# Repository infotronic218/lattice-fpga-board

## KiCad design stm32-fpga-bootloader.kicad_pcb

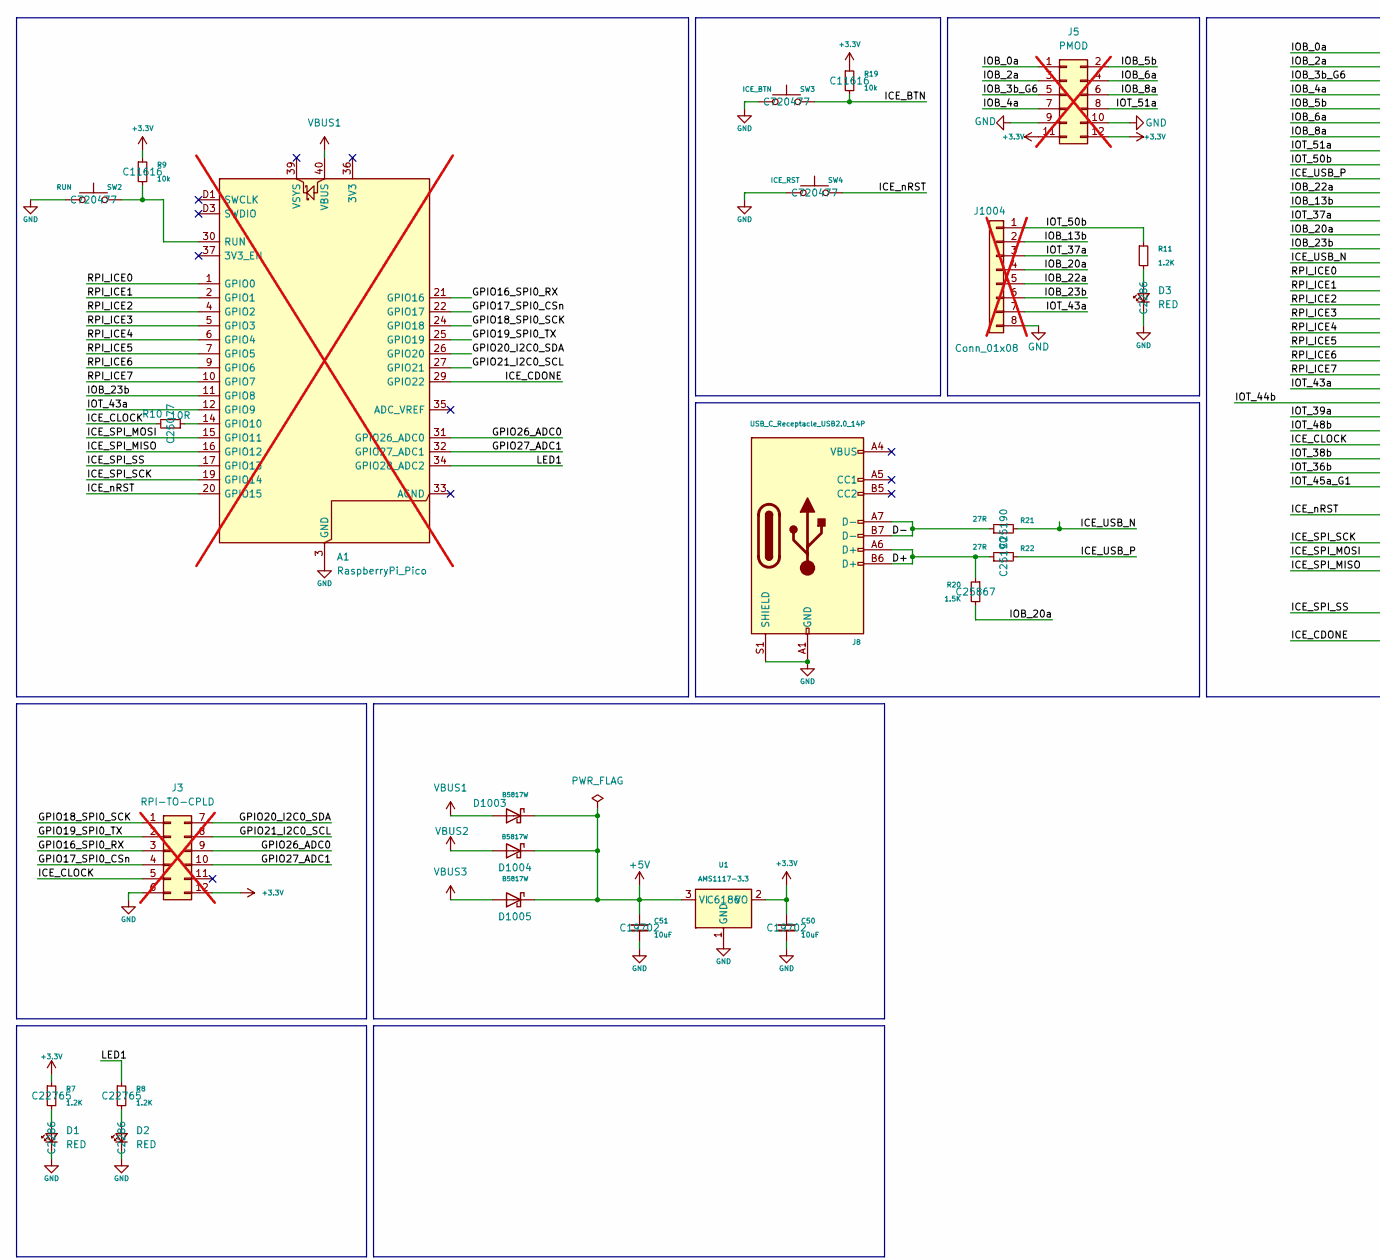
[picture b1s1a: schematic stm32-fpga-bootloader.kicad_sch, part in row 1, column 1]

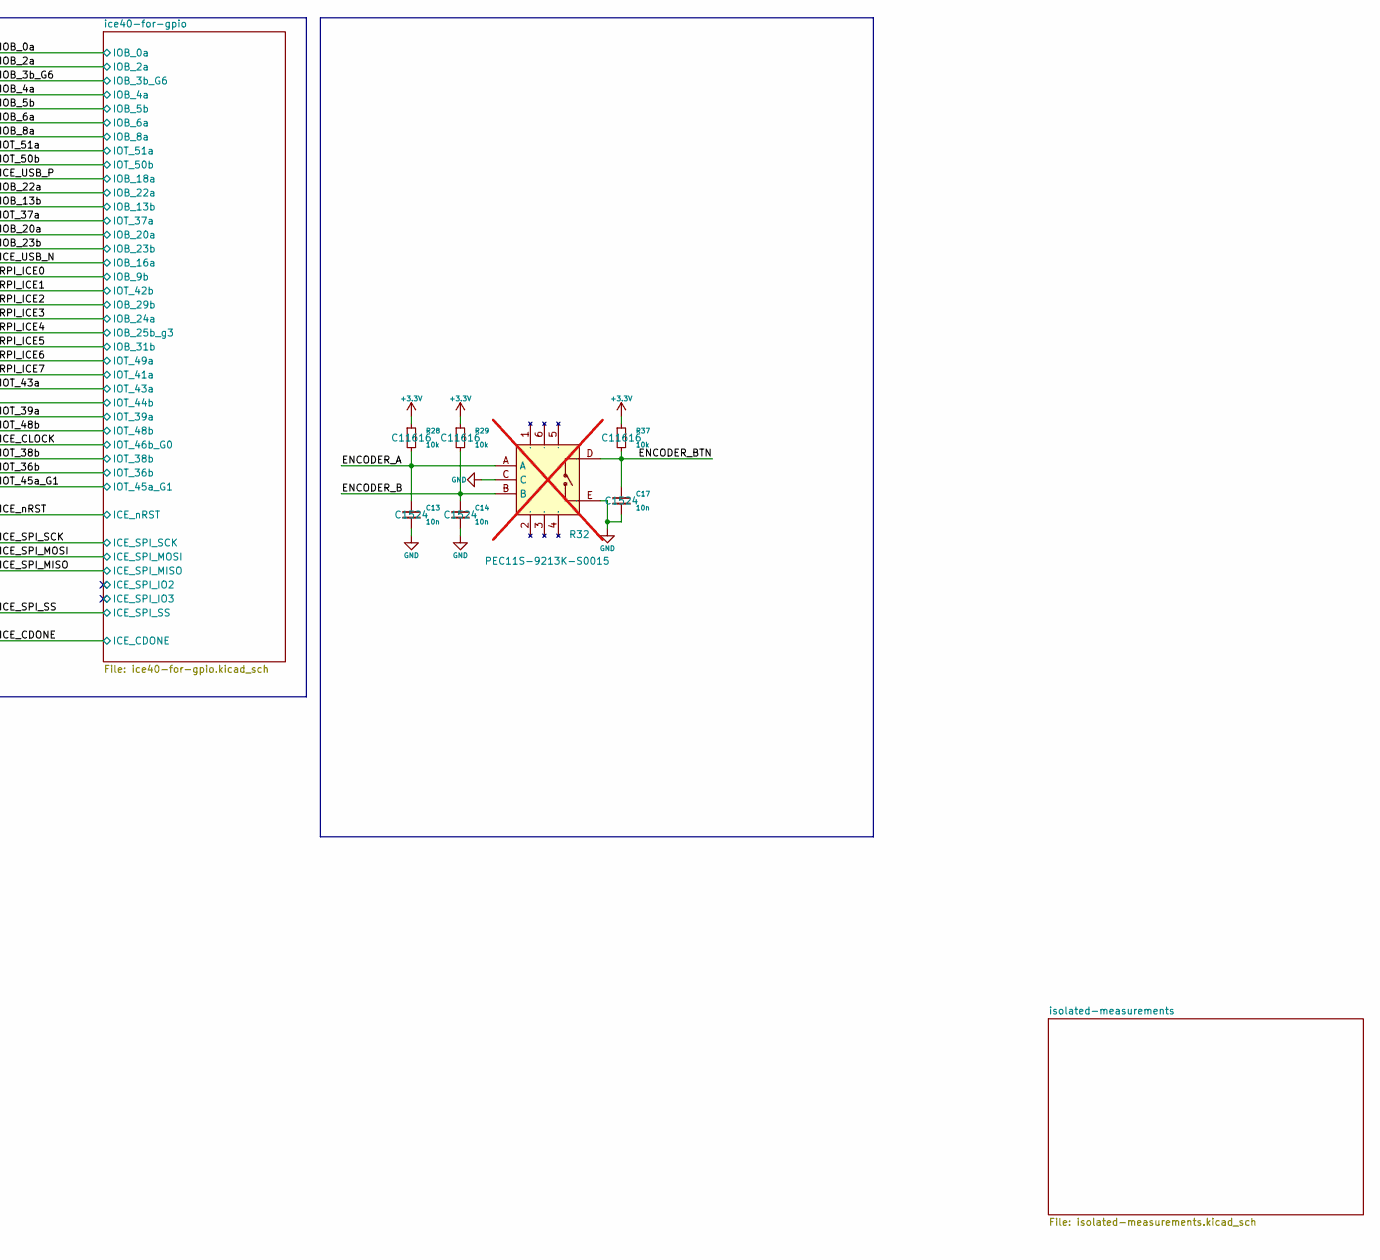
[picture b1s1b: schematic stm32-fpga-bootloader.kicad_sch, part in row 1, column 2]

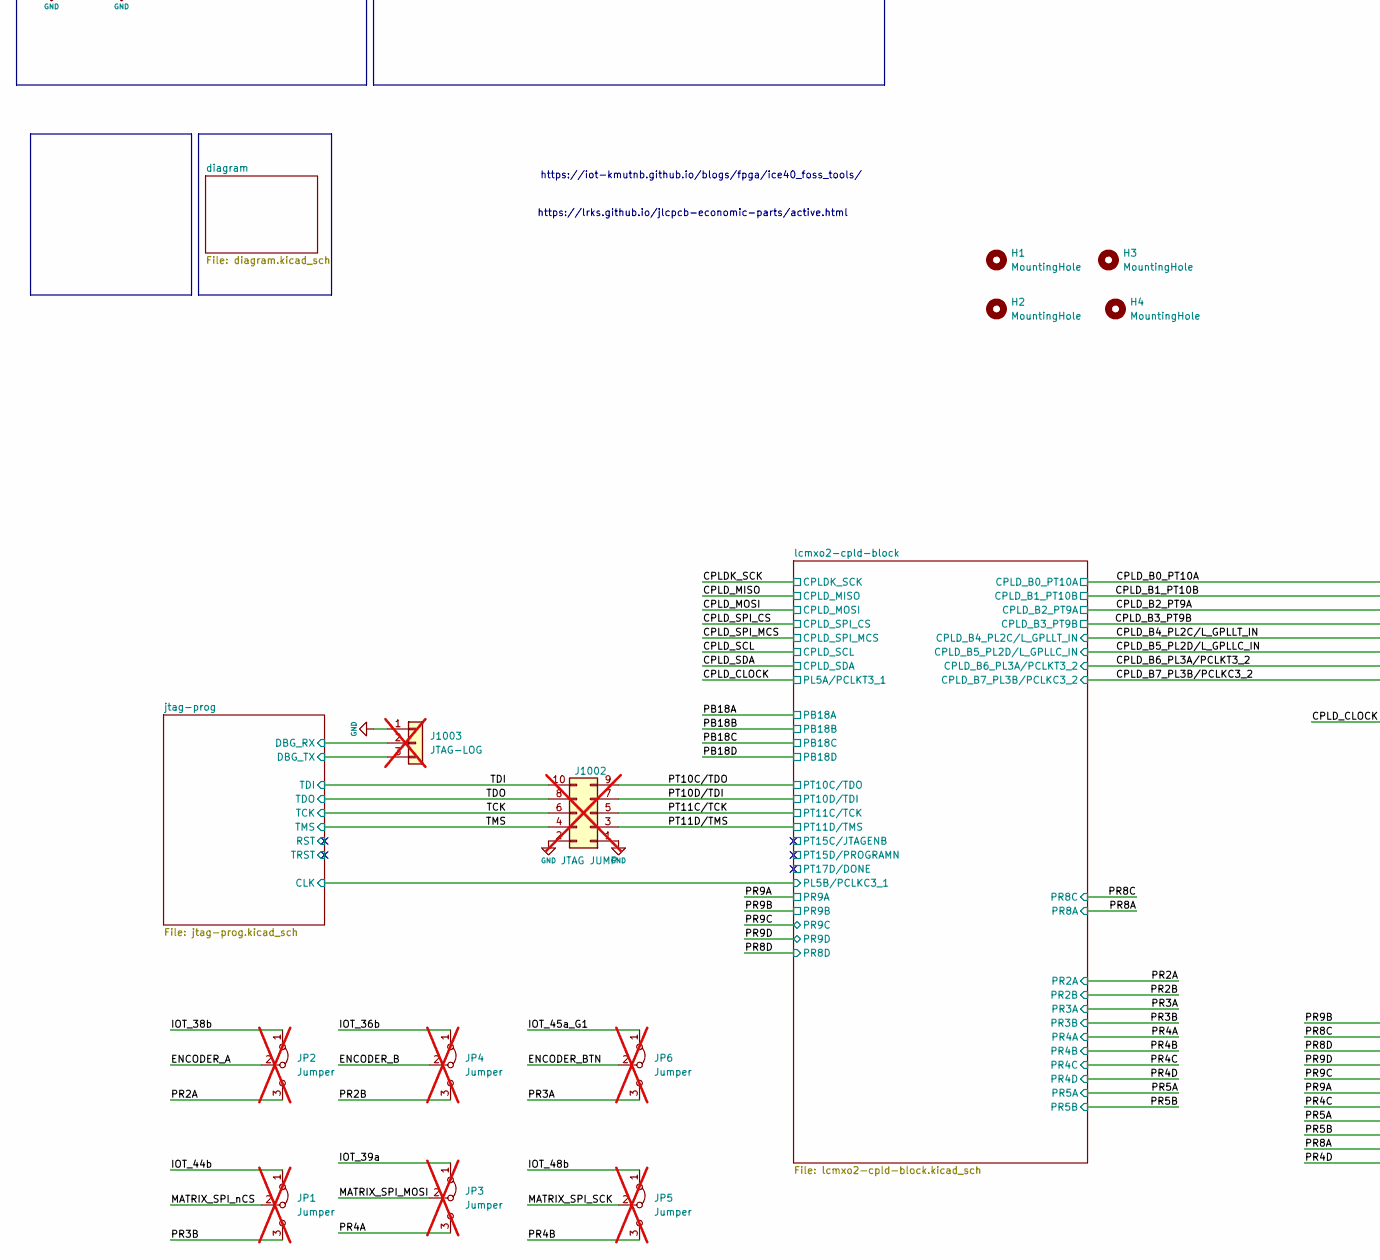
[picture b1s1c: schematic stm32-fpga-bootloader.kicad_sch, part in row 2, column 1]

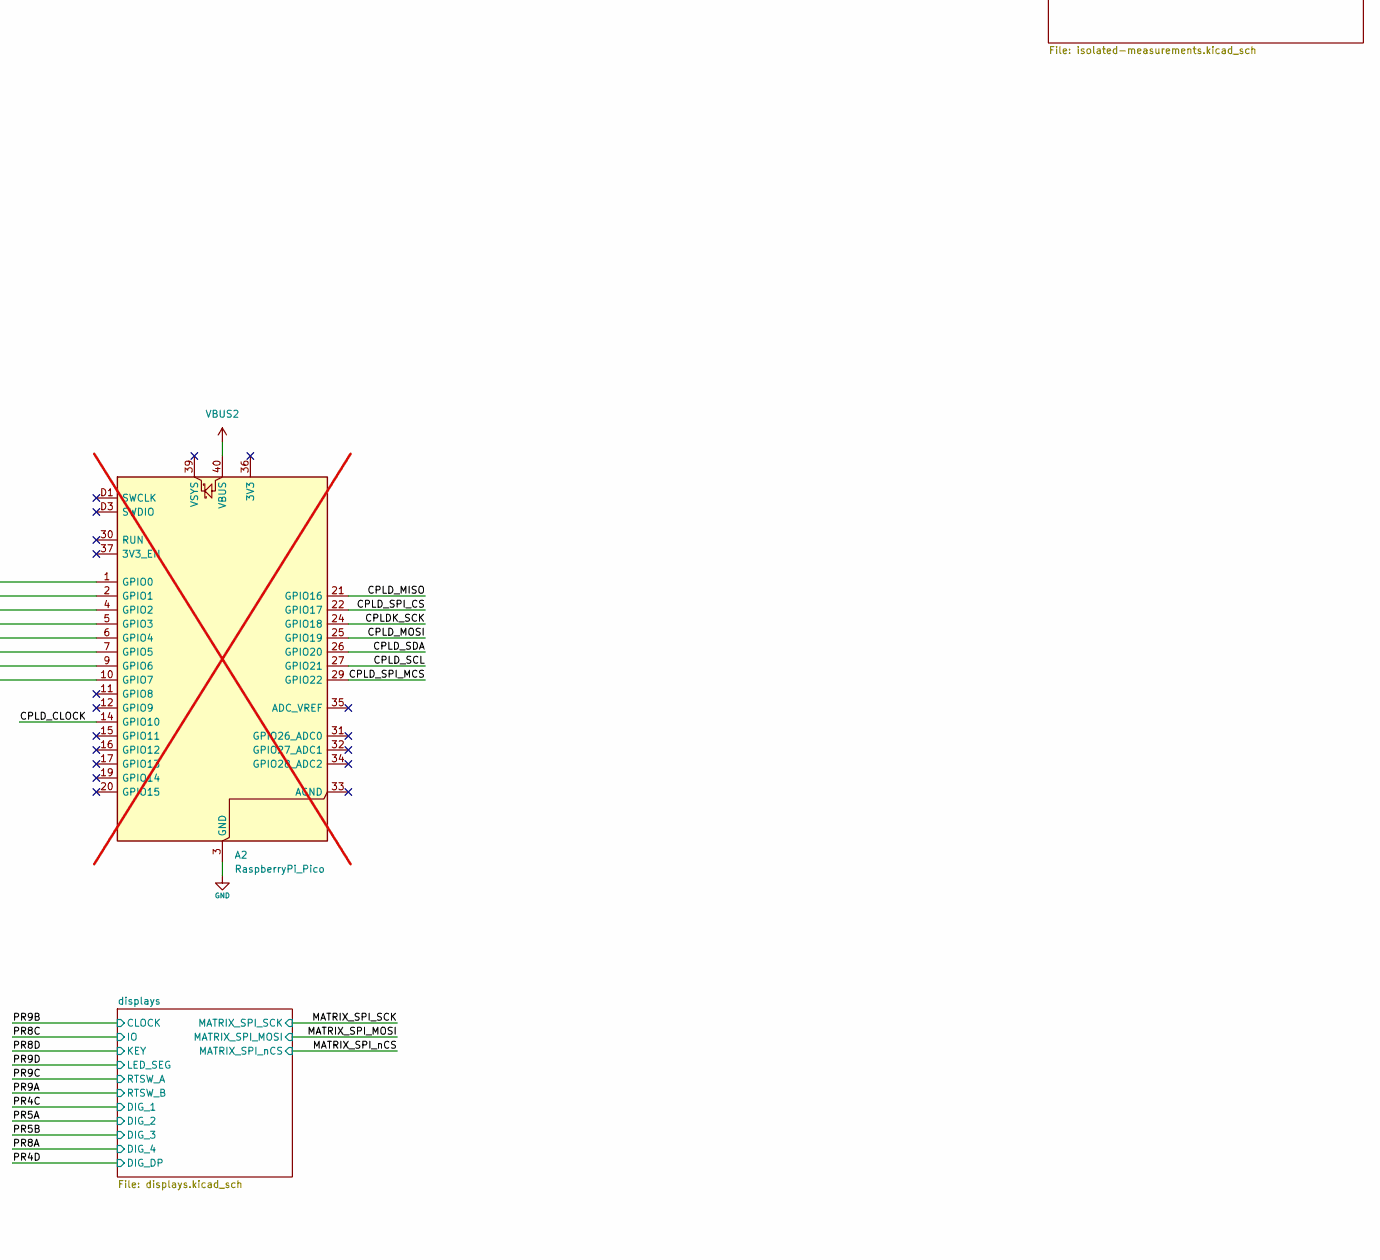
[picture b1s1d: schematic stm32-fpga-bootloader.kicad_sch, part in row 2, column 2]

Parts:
A1, A2: RaspberryPi_Pico; RaspberryPi_Pico_Common_THT; not fitted
C13, C14, C17: 10n; C_0402_1005Metric; LCSC C1524
C50, C51: 10uF; C_0603_1608Metric; LCSC C19702
D1, D2, D3: RED; LED_0603_1608Metric; LCSC C2286
D1003, D1004, D1005: B5817W; D_SOD-123; LCSC C7420328
H1, H2, H3, H4: MountingHole; MountingHole_3.2mm_M3
J3: RPI-TO-CPLD; PinHeader_2x06_P2.54mm_Vertical; not fitted
J5: PMOD; PinSocket_2x06_P2.54mm_Horizontal; not fitted
J8: USB_C_Receptacle_USB2.0_14P; USB_C_Receptacle_G-Switch_GT-USB-7010ASV
J1002: JTAG JUMP; PinSocket_2x05_P2.54mm_Vertical; not fitted
J1003: JTAG-LOG; PinSocket_1x03_P2.54mm_Vertical; not fitted
J1004: Conn_01x08; PinHeader_1x08_P2.54mm_Vertical; not fitted
JP1, JP2, JP3, JP4, JP5, JP6: Jumper; PinSocket_1x03_P1.27mm_Vertical; not fitted
R7, R8, R11: 1.2K; R_0603_1608Metric; LCSC C22765
R9, R19, R28, R29, R37: 10k; R_0402_1005Metric; LCSC C11616
R10: 10R; R_0402_1005Metric; LCSC C25077
R20: 1.5K; R_0402_1005Metric; LCSC C25867
R21, R22: 27R; R_0603_1608Metric; LCSC C25190
R32: PEC11S-9213K-S0015; RES-ADJ-SMD_PEC11S-9213K-S0015; LCSC Part Name PEC11S-9213K-S0015; not fitted
SW2: RUN; SW-SMD_L3.9-W3.0-P4.45; LCSC C720477
SW3: ICE_BTN; SW-SMD_L3.9-W3.0-P4.45; LCSC C720477
SW4: ICE_RST; SW-SMD_L3.9-W3.0-P4.45; LCSC C720477
U1: AMS1117-3.3; SOT-223-3_TabPin2; LCSC C6186

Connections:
+3.3V: C50.1, J3.12, J5.11, J5.12, R7.1, R9.1, R19.1, R28.1, R29.1, R37.1, U1.2 (VO); also elsewhere on the board
+5V: C51.1, D1003.1, D1004.1, D1005.1, U1.3 (VI); also elsewhere on the board
/CPLDK_SCK: A2.24 (GPIO18); also elsewhere on the board
/CPLD_B0_PT10A: A2.1 (GPIO0); also elsewhere on the board
/CPLD_B1_PT10B: A2.2 (GPIO1); also elsewhere on the board
/CPLD_B2_PT9A: A2.4 (GPIO2); also elsewhere on the board
/CPLD_B3_PT9B: A2.5 (GPIO3); also elsewhere on the board
/CPLD_B4_PL2C/L_GPLLT_IN: A2.6 (GPIO4); also elsewhere on the board
/CPLD_B5_PL2D/L_GPLLC_IN: A2.7 (GPIO5); also elsewhere on the board
/CPLD_B6_PL3A/PCLKT3_2: A2.9 (GPIO6); also elsewhere on the board
/CPLD_B7_PL3B/PCLKC3_2: A2.10 (GPIO7); also elsewhere on the board
/CPLD_CLOCK: A2.14 (GPIO10); also elsewhere on the board
/CPLD_MISO: A2.21 (GPIO16); also elsewhere on the board
/CPLD_MOSI: A2.25 (GPIO19); also elsewhere on the board
/CPLD_SCL: A2.27 (GPIO21); also elsewhere on the board
/CPLD_SDA: A2.26 (GPIO20); also elsewhere on the board
/CPLD_SPI_CS: A2.22 (GPIO17); also elsewhere on the board
/CPLD_SPI_MCS: A2.29 (GPIO22); also elsewhere on the board
/D+: J8.A6 (D+), J8.B6 (D+), R20.1, R22.1
/D-: J8.A7 (D-), J8.B7 (D-), R21.1
/ENCODER_A: C13.1, JP2.2 (C), R28.2, R32.A
/ENCODER_B: C14.1, JP4.2 (C), R29.2, R32.B
/ENCODER_BTN: C17.1, JP6.2 (C), R32.D, R37.2
/GPIO16_SPI0_RX: A1.21 (GPIO16), J3.3
/GPIO17_SPI0_CSn: A1.22 (GPIO17), J3.4
/GPIO18_SPI0_SCK: A1.24 (GPIO18), J3.1
/GPIO19_SPI0_TX: A1.25 (GPIO19), J3.2
/GPIO20_I2C0_SDA: A1.26 (GPIO20), J3.7
/GPIO21_I2C0_SCL: A1.27 (GPIO21), J3.8
/GPIO26_ADC0: A1.31 (GPIO26_ADC0), J3.9
/GPIO27_ADC1: A1.32 (GPIO27_ADC1), J3.10
/ICE_BTN: R19.2, SW3.2
/ICE_CDONE: A1.29 (GPIO22); also elsewhere on the board
/ICE_CLOCK: J3.5, R10.2; also elsewhere on the board
/ICE_SPI_MISO: A1.16 (GPIO12); also elsewhere on the board
/ICE_SPI_MOSI: A1.15 (GPIO11); also elsewhere on the board
/ICE_SPI_SCK: A1.19 (GPIO14); also elsewhere on the board
/ICE_SPI_SS: A1.17 (GPIO13); also elsewhere on the board
/ICE_USB_N: R21.2; also elsewhere on the board
/ICE_USB_P: R22.2; also elsewhere on the board
/ICE_nRST: A1.20 (GPIO15), SW4.2; also elsewhere on the board
/IOB_0a: J5.1; also elsewhere on the board
/IOB_2a: J5.3; also elsewhere on the board
/IOB_3b_G6: J5.5; also elsewhere on the board
/IOB_4a: J5.7; also elsewhere on the board
/IOB_5b: J5.2; also elsewhere on the board
/IOB_6a: J5.4; also elsewhere on the board
/IOB_8a: J5.6; also elsewhere on the board
/IOB_13b: J1004.2; also elsewhere on the board
/IOB_20a: J1004.4, R20.2; also elsewhere on the board
/IOB_22a: J1004.5; also elsewhere on the board
/IOB_23b: A1.11 (GPIO8), J1004.6; also elsewhere on the board
/IOT_36b: JP4.1 (A); also elsewhere on the board
/IOT_37a: J1004.3; also elsewhere on the board
/IOT_38b: JP2.1 (A); also elsewhere on the board
/IOT_39a: JP3.1 (A); also elsewhere on the board
/IOT_43a: A1.12 (GPIO9), J1004.7; also elsewhere on the board
/IOT_44b: JP1.1 (A); also elsewhere on the board
/IOT_45a_G1: JP6.1 (A); also elsewhere on the board
/IOT_48b: JP5.1 (A); also elsewhere on the board
/IOT_50b: J1004.1, R11.1; also elsewhere on the board
/IOT_51a: J5.8; also elsewhere on the board
/LED1: A1.34 (GPIO28_ADC2), R8.1
/MATRIX_SPI_MOSI: JP3.2 (C); also elsewhere on the board
/MATRIX_SPI_SCK: JP5.2 (C); also elsewhere on the board
/MATRIX_SPI_nCS: JP1.2 (C); also elsewhere on the board
/PR2A: JP2.3 (B); also elsewhere on the board
/PR2B: JP4.3 (B); also elsewhere on the board
/PR3A: JP6.3 (B); also elsewhere on the board
/PR3B: JP1.3 (B); also elsewhere on the board
/PR4A: JP3.3 (B); also elsewhere on the board
/PR4B: JP5.3 (B); also elsewhere on the board
/PT10C/TDO: J1002.9; also elsewhere on the board
/PT10D/TDI: J1002.7; also elsewhere on the board
/PT11C/TCK: J1002.5; also elsewhere on the board
/PT11D/TMS: J1002.3; also elsewhere on the board
/RPI_ICE0: A1.1 (GPIO0); also elsewhere on the board
/RPI_ICE1: A1.2 (GPIO1); also elsewhere on the board
/RPI_ICE2: A1.4 (GPIO2); also elsewhere on the board
/RPI_ICE3: A1.5 (GPIO3); also elsewhere on the board
/RPI_ICE4: A1.6 (GPIO4); also elsewhere on the board
/RPI_ICE5: A1.7 (GPIO5); also elsewhere on the board
/RPI_ICE6: A1.9 (GPIO6); also elsewhere on the board
/RPI_ICE7: A1.10 (GPIO7); also elsewhere on the board
/TCK: J1002.6; also elsewhere on the board
/TDI: J1002.10; also elsewhere on the board
/TDO: J1002.8; also elsewhere on the board
/TMS: J1002.4; also elsewhere on the board
/jtag-prog/DBG_RX: J1003.2; also elsewhere on the board
/jtag-prog/DBG_TX: J1003.3; also elsewhere on the board
GND: A1.3 (GND), A1.8 (GND), A1.13 (GND), A1.18 (GND), A1.23 (GND), A1.28 (GND), A1.38 (GND), A1.D2 (GND), A2.3 (GND), A2.8 (GND), A2.13 (GND), A2.18 (GND), A2.23 (GND), A2.28 (GND), A2.38 (GND), A2.D2 (GND), C13.2, C14.2, C17.2, C50.2, C51.2, D1.1 (K), D2.1 (K), D3.1 (K), J3.6, J5.9, J5.10, J8.A1 (GND), J8.A12 (GND), J8.B1 (GND), J8.B12 (GND), J8.S1 (SHIELD), J1002.1, J1002.2, J1003.1, J1004.8, R32.C, R32.E, SW2.1, SW3.1, SW4.1, U1.1 (GND); also elsewhere on the board
unnamed: A1.14 (GPIO10), R10.1
unnamed: A1.30 (RUN), R9.2, SW2.2
unnamed: D1.2 (A), R7.2
unnamed: D2.2 (A), R8.2
unnamed: D3.2 (A), R11.2
VBUS1: A1.40 (VBUS), D1003.2
VBUS2: A2.40 (VBUS), D1004.2
VBUS3: D1005.2; also elsewhere on the board

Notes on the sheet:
https://iot-kmutnb.github.io/blogs/fpga/ice40_foss_tools/
https://lrks.github.io/jlcpcb-economic-parts/active.html

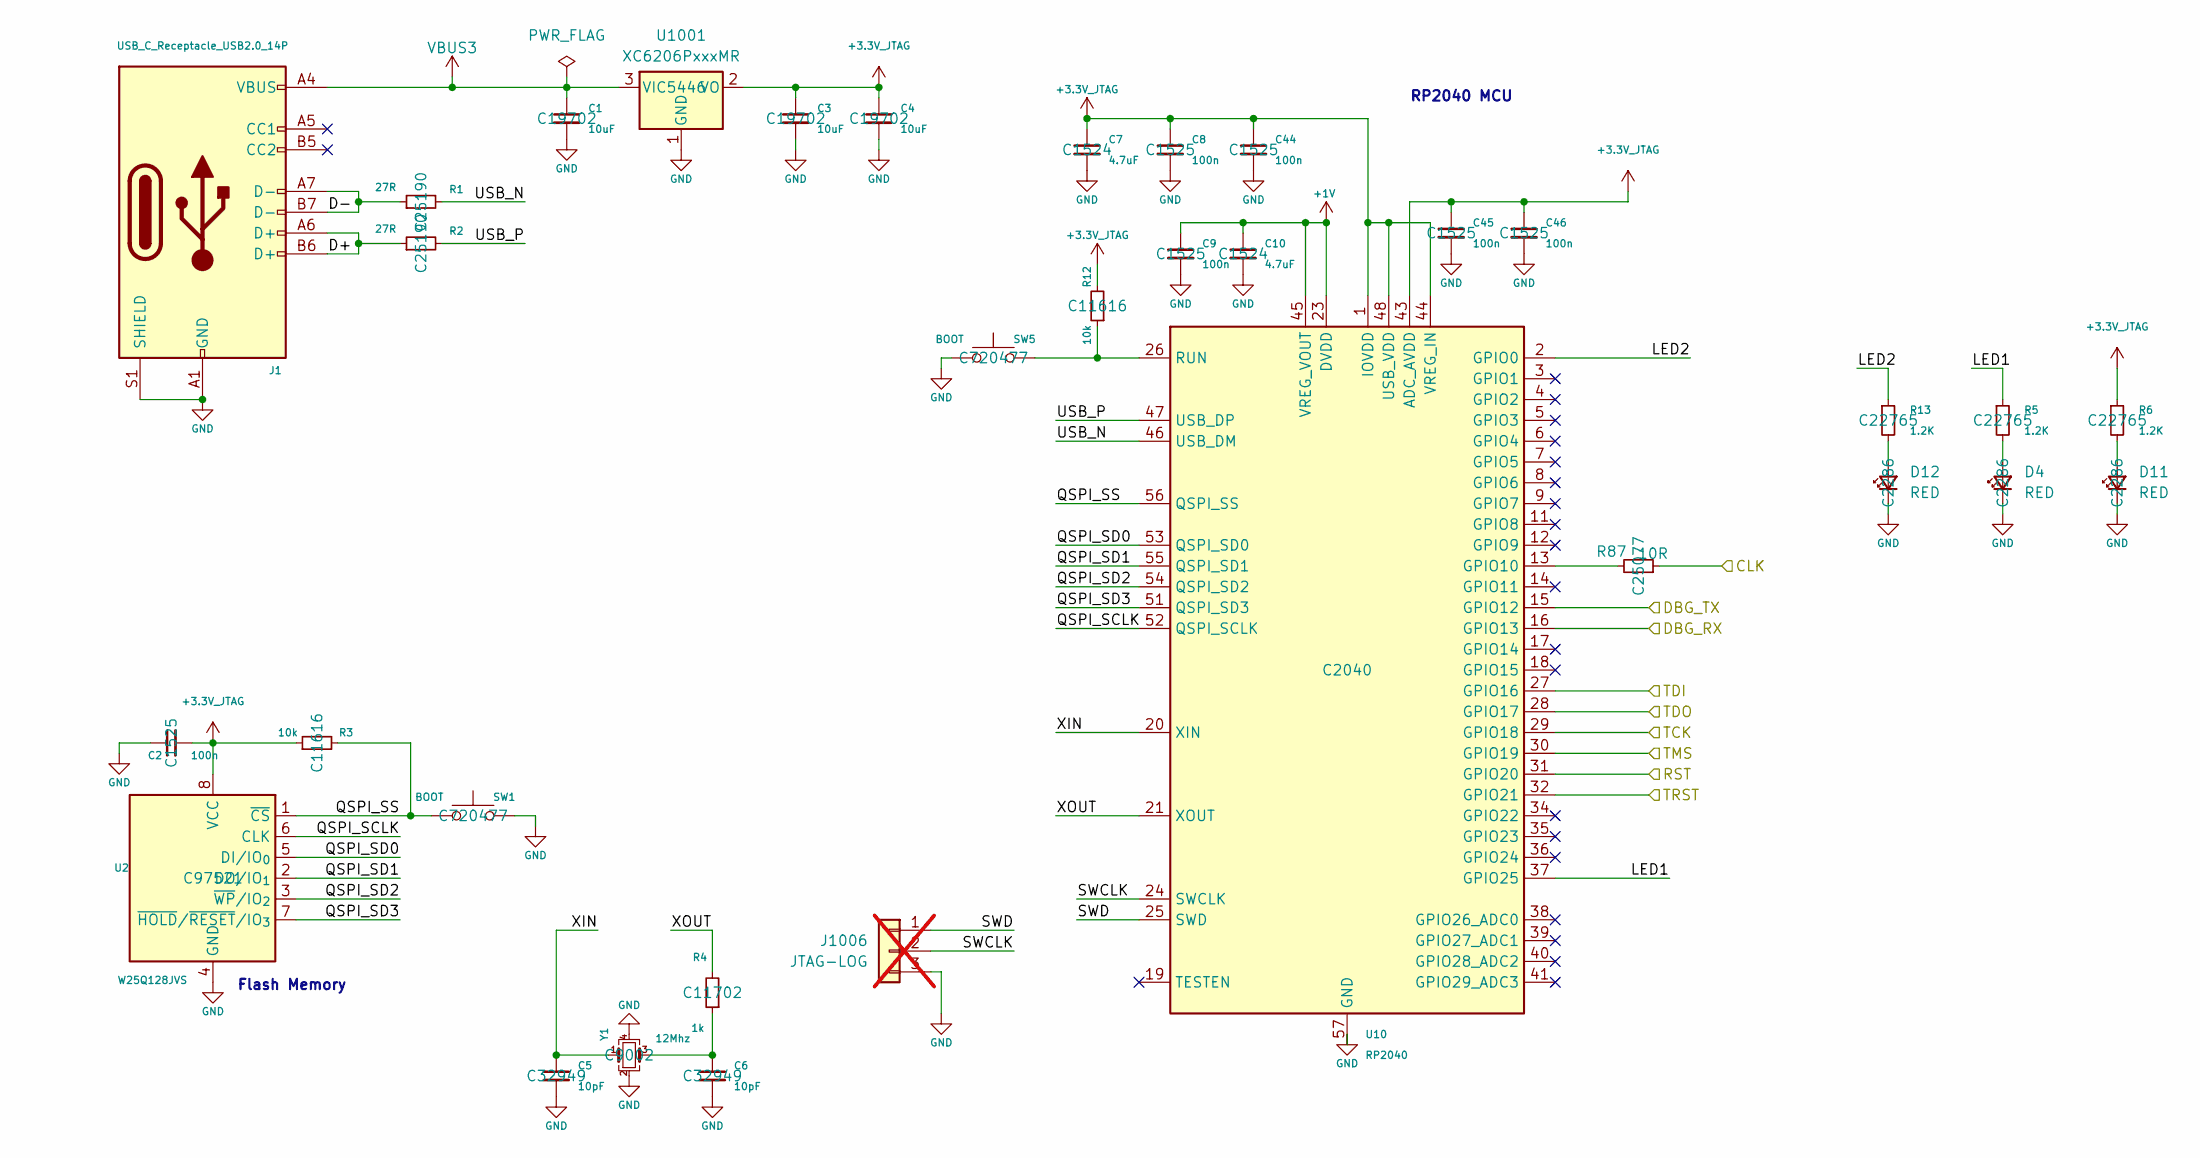
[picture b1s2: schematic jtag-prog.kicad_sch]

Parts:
C1, C3, C4: 10uF; C_0603_1608Metric; LCSC C19702
C2, C8, C9, C44, C45, C46: 100n; C_0402_1005Metric; LCSC C1525
C5, C6: 10pF; C_0402_1005Metric; LCSC C32949
C7, C10: 4.7uF; C_0603_1608Metric; LCSC C1524
D4, D11, D12: RED; LED_0603_1608Metric; LCSC C2286
J1: USB_C_Receptacle_USB2.0_14P; USB_C_Receptacle_G-Switch_GT-USB-7010ASV
J1006: JTAG-LOG; PinSocket_1x03_P2.54mm_Vertical; not fitted
R1, R2: 27R; R_0603_1608Metric; LCSC C25190
R3, R12: 10k; R_0402_1005Metric; LCSC C11616
R4: 1k; R_0402_1005Metric; LCSC C11702
R5, R6, R13: 1.2K; R_0603_1608Metric; LCSC C22765
R87: 10R; R_0402_1005Metric; LCSC C25077
SW1, SW5: BOOT; SW-SMD_L3.9-W3.0-P4.45; LCSC C720477
U2: W25Q128JVS; SOIC-8_5.3x5.3mm_P1.27mm; LCSC C97521
U10: RP2040; QFN-56-1EP_7x7mm_P0.4mm_EP3.2x3.2mm; LCSC C2040
U1001: XC6206PxxxMR; SOT-23-3; LCSC C5446
Y1: 12Mhz; Crystal_SMD_3225-4Pin_3.2x2.5mm; LCSC C9002

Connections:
+1V: C9.1, C10.1, U10.23 (DVDD), U10.45 (VREG_VOUT), U10.50 (DVDD)
+3.3V_JTAG: C2.2, C3.1, C4.1, C7.1, C8.1, C44.1, C45.1, C46.1, R3.1, R6.1, R12.2, U2.8 (VCC), U10.1 (IOVDD), U10.10 (IOVDD), U10.22 (IOVDD), U10.33 (IOVDD), U10.42 (IOVDD), U10.43 (ADC_AVDD), U10.44 (VREG_IN), U10.48 (USB_VDD), U10.49 (IOVDD), U1001.2 (VO)
/TCK: U10.29 (GPIO18); also elsewhere on the board
/TDI: U10.27 (GPIO16); also elsewhere on the board
/TDO: U10.28 (GPIO17); also elsewhere on the board
/TMS: U10.30 (GPIO19); also elsewhere on the board
/jtag-prog/CLK: R87.1; also elsewhere on the board
/jtag-prog/D+: J1.A6 (D+), J1.B6 (D+), R2.1
/jtag-prog/D-: J1.A7 (D-), J1.B7 (D-), R1.1
/jtag-prog/DBG_RX: U10.16 (GPIO13); also elsewhere on the board
/jtag-prog/DBG_TX: U10.15 (GPIO12); also elsewhere on the board
/jtag-prog/LED1: R5.1, U10.37 (GPIO25)
/jtag-prog/LED2: R13.1, U10.2 (GPIO0)
/jtag-prog/QSPI_SCLK: U2.6 (CLK), U10.52 (QSPI_SCLK)
/jtag-prog/QSPI_SD0: U2.5 (DI/IO_{0}), U10.53 (QSPI_SD0)
/jtag-prog/QSPI_SD1: U2.2 (DO/IO_{1}), U10.55 (QSPI_SD1)
/jtag-prog/QSPI_SD2: U2.3 (~WP/IO_{2}), U10.54 (QSPI_SD2)
/jtag-prog/QSPI_SD3: U2.7 (~HOLD/~RESET/IO_{3}), U10.51 (QSPI_SD3)
/jtag-prog/QSPI_SS: R3.2, SW1.1, U2.1 (~CS), U10.56 (QSPI_SS)
/jtag-prog/RST: U10.31 (GPIO20)
/jtag-prog/SWCLK: J1006.2, U10.24 (SWCLK)
/jtag-prog/SWD: J1006.1, U10.25 (SWD)
/jtag-prog/TRST: U10.32 (GPIO21)
/jtag-prog/USB_N: R1.2, U10.46 (USB_DM)
/jtag-prog/USB_P: R2.2, U10.47 (USB_DP)
/jtag-prog/XIN: C5.1, U10.20 (XIN), Y1.1
/jtag-prog/XOUT: R4.2, U10.21 (XOUT)
GND: C1.2, C2.1, C3.2, C4.2, C5.2, C6.2, C7.2, C8.2, C9.2, C10.2, C44.2, C45.2, C46.2, D4.1 (K), D11.1 (K), D12.1 (K), J1.A1 (GND), J1.A12 (GND), J1.B1 (GND), J1.B12 (GND), J1.S1 (SHIELD), J1006.3, SW1.2, SW5.1, U2.4 (GND), U10.57 (GND), U1001.1 (GND), Y1.2, Y1.4; also elsewhere on the board
unnamed: C6.1, R4.1, Y1.3
unnamed: D4.2 (A), R5.2
unnamed: D11.2 (A), R6.2
unnamed: D12.2 (A), R13.2
unnamed: R87.2, U10.13 (GPIO10)
unnamed: R12.1, SW5.2, U10.26 (RUN)
VBUS3: C1.1, J1.A4 (VBUS), J1.A9 (VBUS), J1.B4 (VBUS), J1.B9 (VBUS), U1001.3 (VI); also elsewhere on the board

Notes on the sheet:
RP2040 MCU
Flash Memory

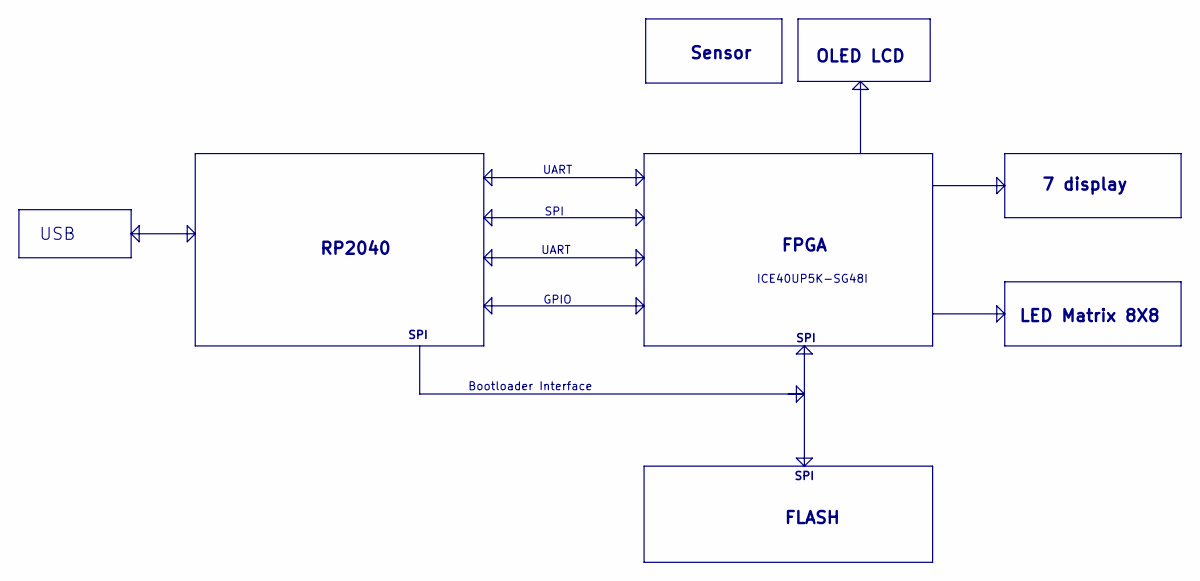
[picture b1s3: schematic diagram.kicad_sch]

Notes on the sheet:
LED Matrix 8X8
OLED LCD
SPI
GPIO
USB
UART
7 display
RP2040
FLASH
Sensor
FPGA
Bootloader Interface
ICE40UP5K-SG48I
